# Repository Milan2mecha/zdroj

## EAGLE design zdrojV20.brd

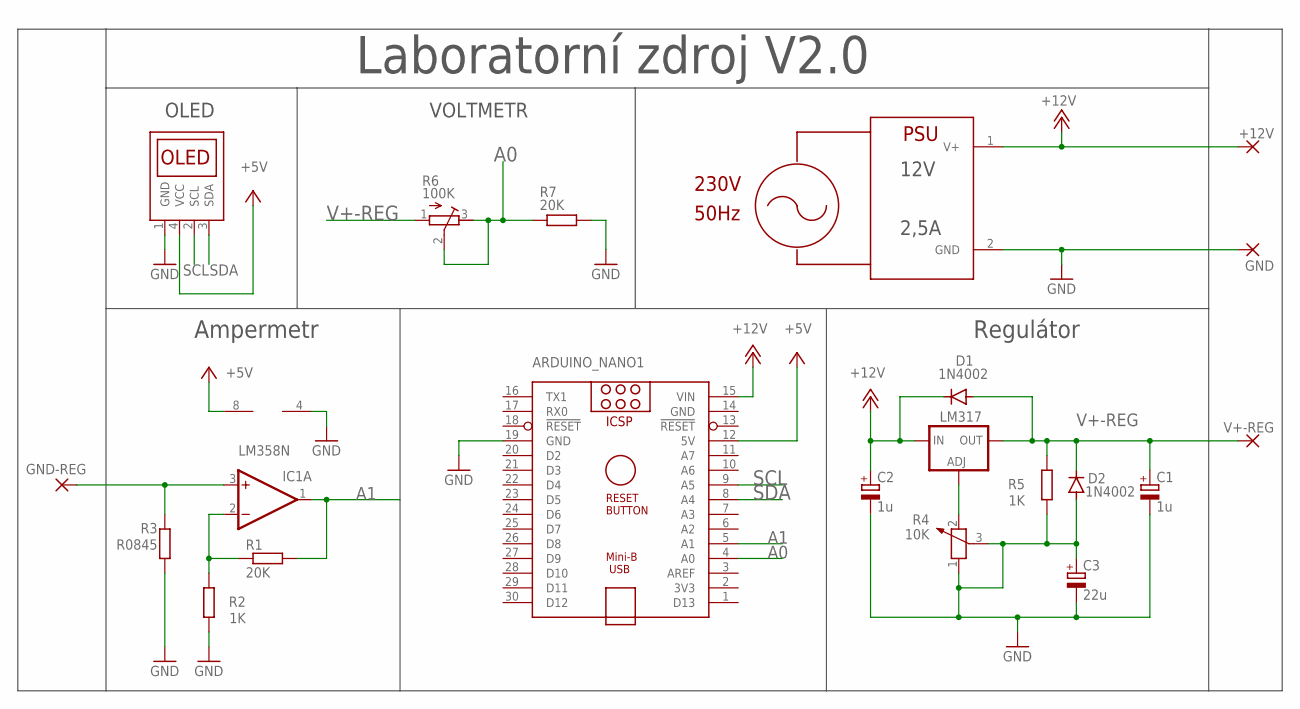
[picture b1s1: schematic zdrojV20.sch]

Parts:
+12V: 3,81/1,4
ARDUINO_NANO1: ARDUINO_NANO
C1, C2: 1u; E2,5-6E
C3: 22u; E2,5-6E
D1, D2: 1N4002; DO41-10
GND: 3,81/1,4
GND-REG: 3,81/1,4
IC1: LM358N; DIL08
IC2: LM317; 317TS
R1, R7: 20K; 0204/7
R2: 1K; 0204/7
R3: R0845; 0414V
R4: 10K; PT-10S
R5: 1K; 0207/10
R6: 100K; RTRIM3339P
U$1: OLEDTWII2C; 1X04
U$2: PSU; 1X02
V+-REG: 3,81/1,4

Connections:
+5V: ARDUINO_NANO1.12 (5V), IC1.8 (V+), U$1.4 (VCC)
+12V: +12V.1, ARDUINO_NANO1.15 (VIN), C2.+, D1.C, IC2.3 (IN), U$2.1 (V+)
A0: ARDUINO_NANO1.4 (A0), R6.2 (S), R6.3 (E), R7.1
A1: ARDUINO_NANO1.5 (A1), IC1.1 (OUT), R1.2
GND: ARDUINO_NANO1.14 (GND), ARDUINO_NANO1.19 (GND), C1.-, C2.-, C3.+, C3.-, D2.A, GND.1, IC1.4 (V-), R2.1, R3.1, R4.1, R4.3, R5.1, R7.2, U$1.1 (GND), U$2.2 (GND)
unnamed: IC1.2 (-IN), R1.1, R2.2
unnamed: GND-REG.1, IC1.3 (+IN), R3.2
unnamed: IC2.1 (ADJ), R4.2
SCL: ARDUINO_NANO1.9 (A5), U$1.2 (SCL)
SDA: ARDUINO_NANO1.8 (A4), U$1.3 (SDA)
V+-REG: C1.+, D1.A, D2.C, IC2.2 (OUT), R5.2, R6.1 (A), V+-REG.1

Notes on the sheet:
Ampermetr
Regulátor
OLED
VOLTMETR
12V
2,5A
Laboratorní zdroj V2.0

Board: 2 copper layers, 21 parts (0 on the bottom side), 11 nets, no tracks yet.
